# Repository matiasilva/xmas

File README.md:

# xmas

A wearable Christmas tree badge: six PWM-driven LEDs, a pattern button and a
PY32F002B microcontroller, powered by a CR2032.

## Layout

- `hardware/` - KiCad 10 project. Open `hardware/tree.kicad_pro`.
  - `tree.pretty/`, `tree.3dshapes/`, `tree.kicad_sym` - project footprints, 3D models and symbols
  - `checks/` - board checks; run `python3 hardware/checks/pad_check.py` and `python3 hardware/checks/led_sim.py`
- `firmware/` - firmware source goes here. Requirements are in `firmware/TODO.md`.

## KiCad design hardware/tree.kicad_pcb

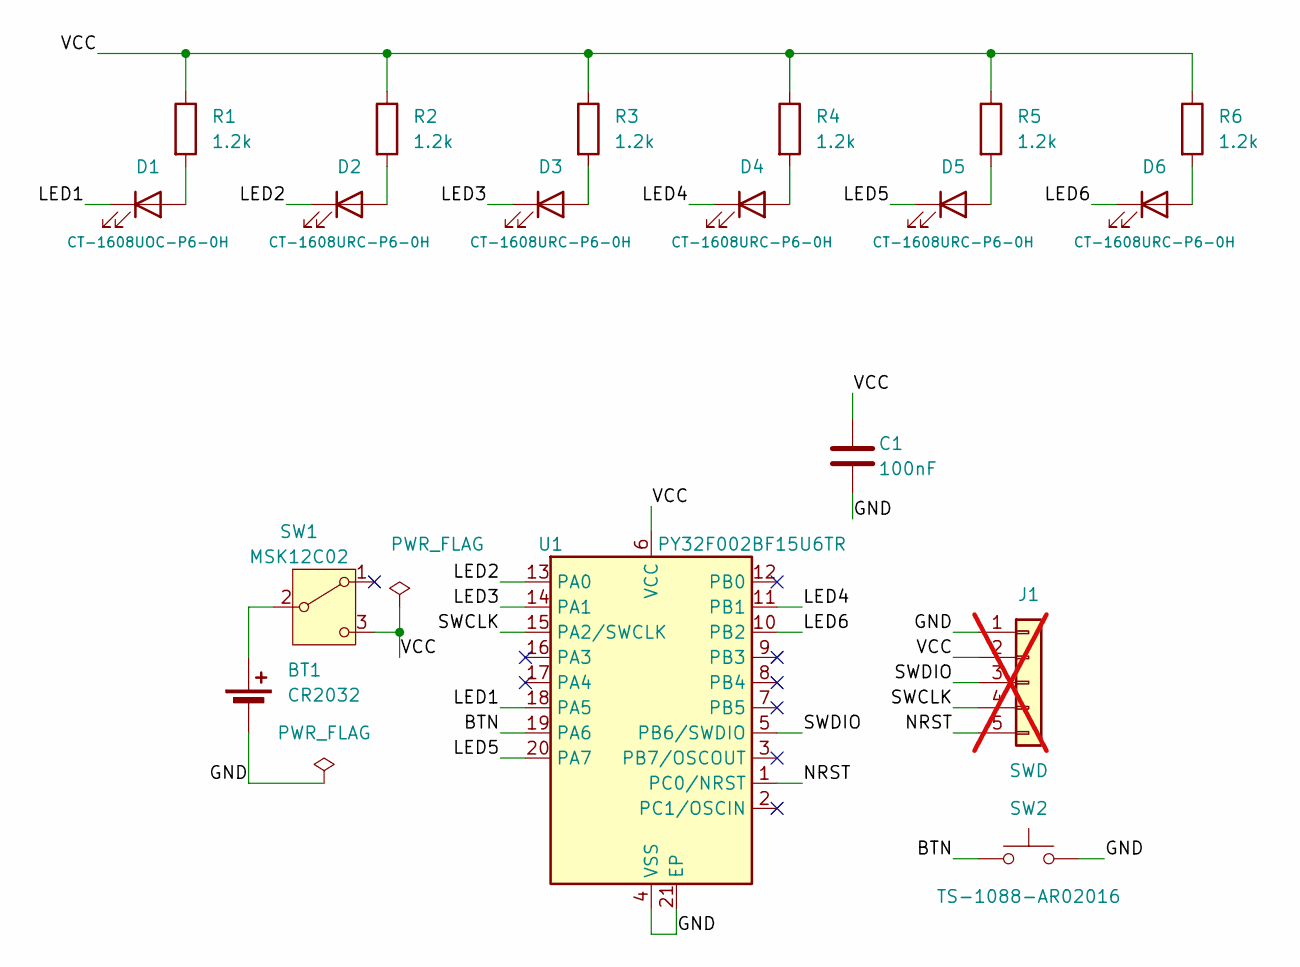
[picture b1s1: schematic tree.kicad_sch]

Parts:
BT1: CR2032; BatteryClip_MYOUNG_MY-2032-16; LCSC C2902340
C1: 100nF; C_0603_1608Metric; LCSC C14663
D1: CT-1608UOC-P6-0H; LED_0603_1608Metric_ReversePolarity; LCSC C52676004
D2, D3, D4, D5, D6: CT-1608URC-P6-0H; LED_0603_1608Metric_ReversePolarity; LCSC C52676005
J1: SWD; PogoPads_2x03_P2.54mm_NoPin6; not fitted
R1, R2, R3, R4, R5, R6: 1.2k; R_0603_1608Metric; LCSC C22765
SW1: MSK12C02; SW_SPDT_Shouhan_MSK12C02; LCSC C431540
SW2: TS-1088-AR02016; SW-SMD_L3.9-W3.0-P4.45; LCSC C720477
U1: PY32F002BF15U6TR; UQFN-20-1EP_3x3mm_P0.4mm_EP1.7x1.7mm; LCSC C7469099

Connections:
/BTN: SW2.1, U1.19 (PA6)
/GND: BT1.2 (-), C1.2, J1.1, SW2.2, U1.4 (VSS), U1.21 (EP)
/LED1: D1.2 (K), U1.18 (PA5)
/LED2: D2.2 (K), U1.13 (PA0)
/LED3: D3.2 (K), U1.14 (PA1)
/LED4: D4.2 (K), U1.11 (PB1)
/LED5: D5.2 (K), U1.20 (PA7)
/LED6: D6.2 (K), U1.10 (PB2)
/NRST: J1.5, U1.1 (PC0/NRST)
/SWCLK: J1.4, U1.15 (PA2/SWCLK)
/SWDIO: J1.3, U1.5 (PB6/SWDIO)
/VCC: C1.1, J1.2, R1.1, R2.1, R3.1, R4.1, R5.1, R6.1, SW1.3 (C), U1.6 (VCC)
unnamed: BT1.1 (+), SW1.2 (B)
unnamed: D1.1 (A), R1.2
unnamed: D2.1 (A), R2.2
unnamed: D3.1 (A), R3.2
unnamed: D4.1 (A), R4.2
unnamed: D5.1 (A), R5.2
unnamed: D6.1 (A), R6.2

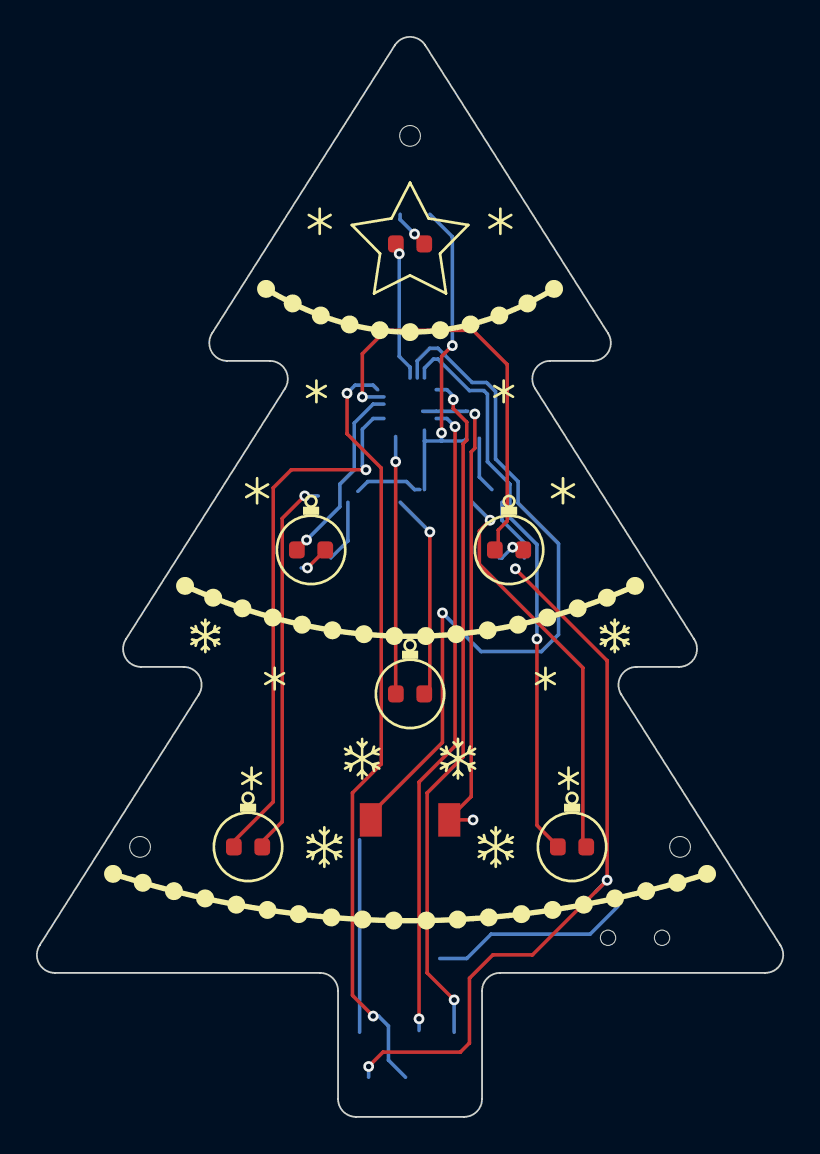
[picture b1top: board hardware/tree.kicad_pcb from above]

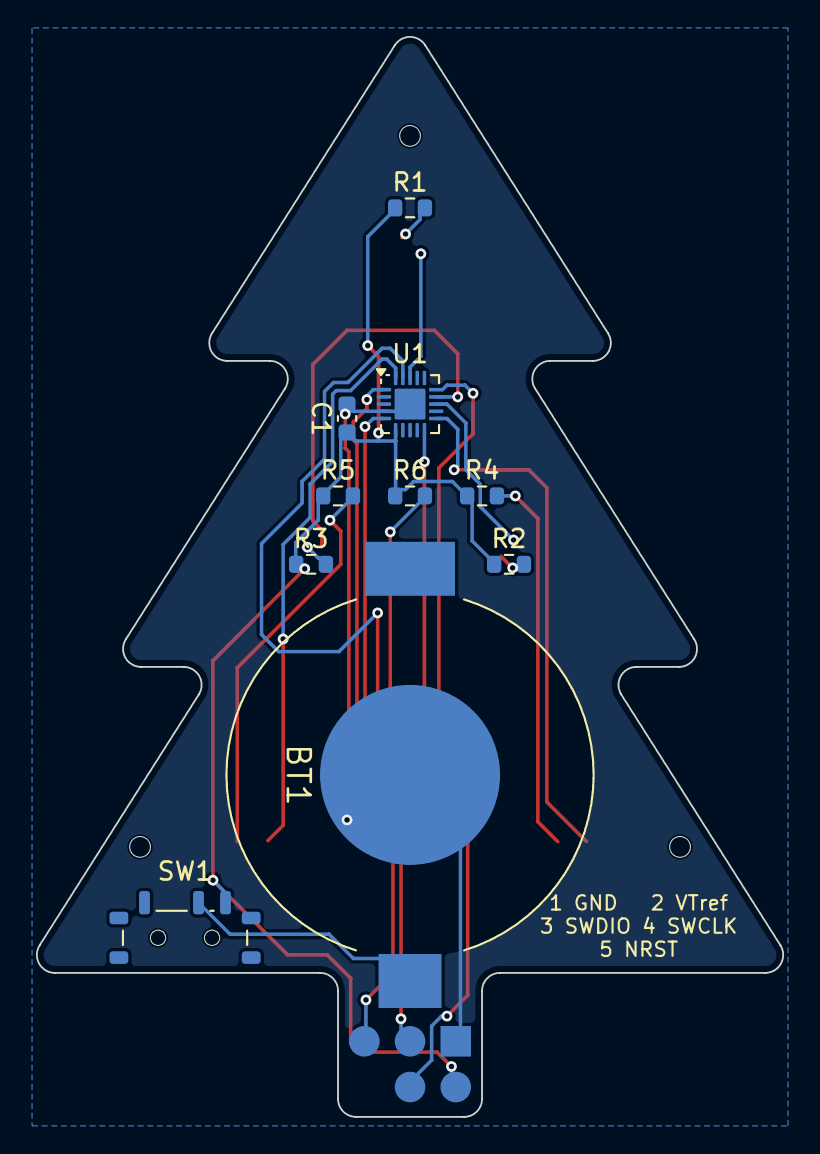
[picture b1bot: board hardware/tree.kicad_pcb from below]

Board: 2 copper layers, 41.5 x 60.0 mm, 21 parts (11 on the bottom side), 19 nets.

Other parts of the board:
TH1, TH2, TH3: Tooling hole; ToolingHole_JLCPCB_1.152mm

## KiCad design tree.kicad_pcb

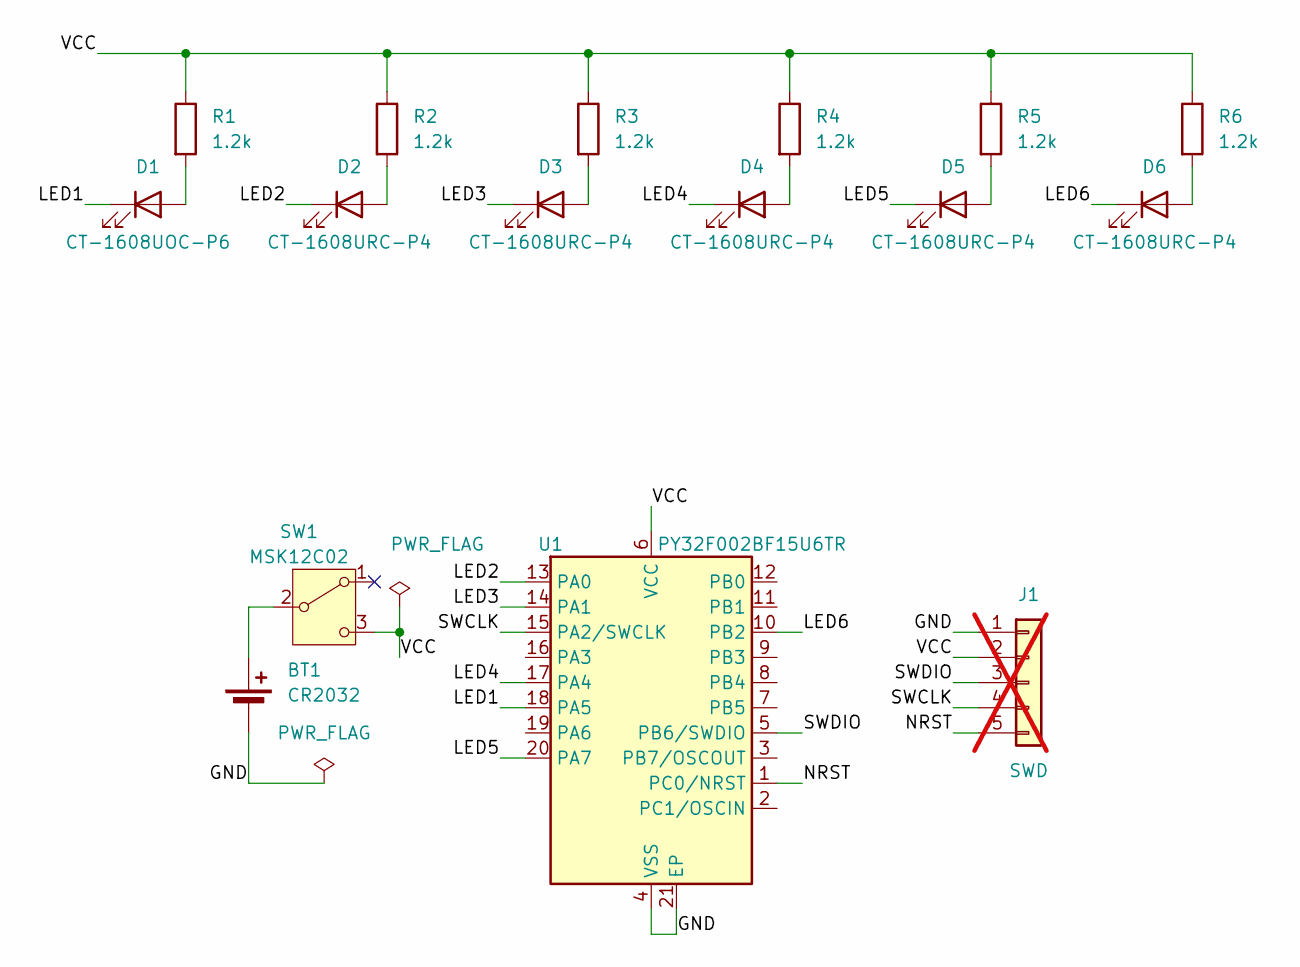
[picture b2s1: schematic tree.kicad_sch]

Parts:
BT1: CR2032; BatteryClip_MYOUNG_MY-2032-16; LCSC C2902340
D1: CT-1608UOC-P6; LED_0603_1608Metric; LCSC C52675993
D2, D3, D4, D5, D6: CT-1608URC-P4; LED_0603_1608Metric; LCSC C52675987
J1: SWD; PinHeader_2x03_P2.54mm_Vertical_NoPin6; not fitted
R1, R2, R3, R4, R5, R6: 1.2k; R_0603_1608Metric
SW1: MSK12C02; SW_SPDT_Shouhan_MSK12C02; LCSC C431540
U1: PY32F002BF15U6TR; UQFN-20-1EP_3x3mm_P0.4mm_EP1.7x1.7mm

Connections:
/GND: BT1.2 (-), J1.1, U1.4 (VSS), U1.21 (EP)
/LED1: D1.1 (K), U1.18 (PA5)
/LED2: D2.1 (K), U1.13 (PA0)
/LED3: D3.1 (K), U1.14 (PA1)
/LED4: D4.1 (K), U1.17 (PA4)
/LED5: D5.1 (K), U1.20 (PA7)
/LED6: D6.1 (K), U1.10 (PB2)
/NRST: J1.5, U1.1 (PC0/NRST)
/SWCLK: J1.4, U1.15 (PA2/SWCLK)
/SWDIO: J1.3, U1.5 (PB6/SWDIO)
/VCC: J1.2, R1.1, R2.1, R3.1, R4.1, R5.1, R6.1, SW1.3 (C), U1.6 (VCC)
unnamed: BT1.1 (+), SW1.2 (B)
unnamed: D1.2 (A), R1.2
unnamed: D2.2 (A), R2.2
unnamed: D3.2 (A), R3.2
unnamed: D4.2 (A), R4.2
unnamed: D5.2 (A), R5.2
unnamed: D6.2 (A), R6.2

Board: 2 copper layers, 17 parts (10 on the bottom side), 18 nets, no tracks yet.

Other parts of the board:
H1: Pin hole; PinHole_1.6mm_NPTH

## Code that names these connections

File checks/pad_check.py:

#!/usr/bin/env python3
"""Datasheet-to-pad check.

Compares what each part's datasheet says about its pins with the net that the
matching pad carries in tree.kicad_pcb.

    python3 checks/pad_check.py [path/to/tree.kicad_pcb]

Exit status is 1 if any check fails. Items that are only correct under a
stated assembly condition are printed as CONDITION and do not fail the run.
"""
import os
import re
import sys

sys.path.insert(0, os.path.dirname(os.path.abspath(__file__)))
from kicad_pcb import Board  # noqa: E402

GND, VCC = '/GND', '/VCC'

# --- Datasheet facts --------------------------------------------------------

# Puya PY32F002B datasheet V1.8, table 3-2, QFN20 column (PY32F002BF15U).
U1_PINS = {
    '1': 'PC0/NRST', '2': 'PC1/OSCIN', '3': 'PB7/OSCOUT', '4': 'VSS',
    '5': 'PB6/SWDIO', '6': 'VCC', '7': 'PB5', '8': 'PB4', '9': 'PB3',
    '10': 'PB2', '11': 'PB1', '12': 'PB0', '13': 'PA0', '14': 'PA1',
    '15': 'PA2/SWCLK', '16': 'PA3', '17': 'PA4', '18': 'PA5', '19': 'PA6',
    '20': 'PA7',
}
# Same datasheet, tables 3-4 and 3-5: timer outputs available on each port pin.
TIMER_OUTPUTS = {
    'PA0': {'TIM1_CH1'}, 'PA1': {'TIM1_CH2'}, 'PA2': {'TIM1_CH4'},
    'PA3': {'TIM1_CH2'}, 'PA4': {'TIM1_CH3', 'TIM14_CH1'},
    'PA5': {'TIM1_CH1', 'TIM14_CH1'}, 'PA6': set(), 'PA7': {'TIM1_CH4'},
    'PB0': {'TIM1_CH2', 'TIM1_CH3N'}, 'PB1': {'TIM1_CH2N', 'TIM1_CH4'},
    'PB2': {'TIM1_CH1N', 'TIM1_CH3'}, 'PB5': {'TIM1_CH3', 'TIM14_CH1'},
    'PB7': {'TIM14_CH1'},
}
# Nets that must sit on a specific U1 pin function.
U1_FIXED = {'VSS': GND, 'VCC': VCC, 'PB6/SWDIO': '/SWDIO',
            'PA2/SWCLK': '/SWCLK', 'PC0/NRST': '/NRST'}
# PWM plan from TODO.md: the timer channel each LED net is meant to use.
PWM_PLAN = {'/LED1': 'TIM14_CH1', '/LED2': 'TIM1_CH1', '/LED3': 'TIM1_CH2',
            '/LED4': 'TIM1_CH4', '/LED5': 'TIM1_CH4', '/LED6': 'TIM1_CH3'}

# Chongtian CT-1608UOC-P6-0H (LCSC C52676004) and CT-1608URC-P6-0H (C52676005):
# both are reverse-polarity parts. Datasheet page 2: pin 1 is the marked end
# and is the anode (+); pin 2 is the cathode (-).
LED_ANODE_PIN = {'CT-1608UOC-P6-0H': '1', 'CT-1608URC-P6-0H': '1'}

# Which board pad the part's pin 1 (marked end) is fitted on. The project
# footprint LED_0603_1608Metric_ReversePolarity numbers its pads to match the
# part, so pin 1 goes on pad 1 and no rotation is needed at assembly.
LED_PIN1_ON_PAD = '1'

# XUNPU TS-1088-AR02016 (LCSC C720477): two-terminal SPST, either way round.
# J1 has no datasheet; it is checked against the silkscreen legend instead.
J1_LEGEND = {'1': GND, '2': VCC, '3': '/SWDIO', '4': '/SWCLK', '5': '/NRST'}
LEGEND_NAMES = {GND: 'GND', VCC: 'VTref', '/SWDIO': 'SWDIO', '/SWCLK': 'SWCLK', '/NRST': 'NRST'}

NOT_CHECKED = {
    'SW1': 'MSK12C02 slide switch: no datasheet has been read for it',
    'BT1': 'MY-2032-16 battery clip: no datasheet has been read for it',
}

results = []


def record(status, ref, text):
    results.append((status, ref, text))


def led_roles(board, ref):
    """Return (anode_pad, cathode_pad) for an LED, from how the board wires it:
    the anode pad is the one that reaches VCC through a resistor."""
    fp = board[ref]
    for pad in ('1', '2'):
        net = fp.net(pad)
        for other_ref, other_pad in board.on_net(net):
            if other_ref.startswith('R'):
                r = board[other_ref]
                far = r.net('2' if other_pad == '1' else '1')
                if far == VCC:
                    return pad, ('2' if pad == '1' else '1')
    raise ValueError('%s: neither pad reaches VCC through a resistor' % ref)


def check_u1(board):
    u1 = board['U1']
    name_net = {}
    for pin, name in U1_PINS.items():
        name_net[name] = u1.net(pin)
    for name, want in U1_FIXED.items():
        pin = [p for p, n in U1_PINS.items() if n == name][0]
        got = name_net[name]
        record('PASS' if got == want else 'FAIL', 'U1',
               'pin %s (%s) carries %s%s' % (pin, name, got, '' if got == want else ', expected ' + want))
    ep = u1.net('21')
    record('PASS' if ep == GND else 'FAIL', 'U1', 'exposed pad carries %s' % ep)
    for net, channel in PWM_PLAN.items():
        pins = [p for p in U1_PINS if u1.net(p) == net]
        if len(pins) != 1:
            record('FAIL', 'U1', '%s is on %d MCU pins' % (net, len(pins)))
            continue
        port = U1_PINS[pins[0]].split('/')[0]
        ok = channel in TIMER_OUTPUTS.get(port, set())
        record('PASS' if ok else 'FAIL', 'U1',
               '%s on pin %s (%s): %s %s' % (net, pins[0], port, channel,
                                              'is available' if ok else 'is NOT available on this pin'))
    used = set(U1_FIXED.values()) | set(PWM_PLAN) | {'/BTN'}
    for pin, name in U1_PINS.items():
        net = u1.net(pin)
        if net not in used and not net.startswith('unconnected-'):
            record('FAIL', 'U1', 'pin %s (%s) carries unexpected net %s' % (pin, name, net))
    btn = [p for p in U1_PINS if u1.net(p) == '/BTN']
    record('PASS' if len(btn) == 1 else 'FAIL', 'U1',
           'button net is on pin %s (%s)' % (btn[0], U1_PINS[btn[0]]) if len(btn) == 1 else 'button net is on %d pins' % len(btn))


def check_leds(board):
    for ref in board.refs('D'):
        fp = board[ref]
        if fp.value not in LED_ANODE_PIN:
            record('FAIL', ref, 'no datasheet data for part %s' % fp.value)
            continue
        anode_pad, cathode_pad = led_roles(board, ref)
        ds_anode = LED_ANODE_PIN[fp.value]
        ds_cathode = '2' if ds_anode == '1' else '1'
        # pad that each datasheet pin lands on under the stated assembly intent
        pin_to_pad = {'1': LED_PIN1_ON_PAD, '2': '2' if LED_PIN1_ON_PAD == '1' else '1'}
        ok = pin_to_pad[ds_anode] == anode_pad and pin_to_pad[ds_cathode] == cathode_pad
        record('PASS' if ok else 'FAIL', ref,
               '%s: datasheet anode (pin %s) on pad %s [%s], cathode on pad %s [%s]' % (
                   fp.value, ds_anode, pin_to_pad[ds_anode], fp.net(pin_to_pad[ds_anode]),
                   pin_to_pad[ds_cathode], fp.net(pin_to_pad[ds_cathode])))
        if LED_PIN1_ON_PAD != '1':
            record('CONDITION', ref,
                   'only correct if the marked end (pin 1) is fitted on pad %s; '
                   'fitted pin 1 on pad 1 it is reversed and will not light' % LED_PIN1_ON_PAD)


def check_sw2(board):
    sw = board['SW2']
    nets = {sw.net('1'), sw.net('2')}
    record('PASS' if nets == {'/BTN', GND} else 'FAIL', 'SW2',
           '%s: terminals carry %s (part is symmetrical)' % (sw.value, ' and '.join(sorted(nets))))


def check_j1(board):
    j1 = board['J1']
    for pad, want in J1_LEGEND.items():
        got = j1.net(pad)
        record('PASS' if got == want else 'FAIL', 'J1',
               'pad %s carries %s%s' % (pad, got, '' if got == want else ', expected ' + want))
    legend = ' '.join(t for t in board.texts if 'SWDIO' in t)
    pairs = dict(re.findall(r'(\d)\s+([A-Za-z]+)', legend))
    want_pairs = {pad: LEGEND_NAMES[net] for pad, net in J1_LEGEND.items()}
    record('PASS' if pairs == want_pairs else 'FAIL', 'J1',
           'silkscreen legend reads %s' % ', '.join('%s %s' % kv for kv in sorted(pairs.items())))


def main():
    here = os.path.dirname(os.path.abspath(__file__))
    path = sys.argv[1] if len(sys.argv) > 1 else os.path.join(here, '..', 'tree.kicad_pcb')
    board = Board(path)
    check_u1(board)
    check_leds(board)
    check_sw2(board)
    check_j1(board)
    for ref, why in NOT_CHECKED.items():
        if ref in board.footprints:
            record('SKIPPED', ref, why)
    width = max(len(r[1]) for r in results)
    for status, ref, text in results:
        print('%-9s %-*s  %s' % (status, width, ref, text))
    counts = {s: sum(1 for r in results if r[0] == s) for s in ('PASS', 'FAIL', 'CONDITION', 'SKIPPED')}
    print('\n%(PASS)d passed, %(FAIL)d failed, %(CONDITION)d conditional, %(SKIPPED)d not checked' % counts)
    return 1 if counts['FAIL'] else 0


if __name__ == '__main__':
    sys.exit(main())
